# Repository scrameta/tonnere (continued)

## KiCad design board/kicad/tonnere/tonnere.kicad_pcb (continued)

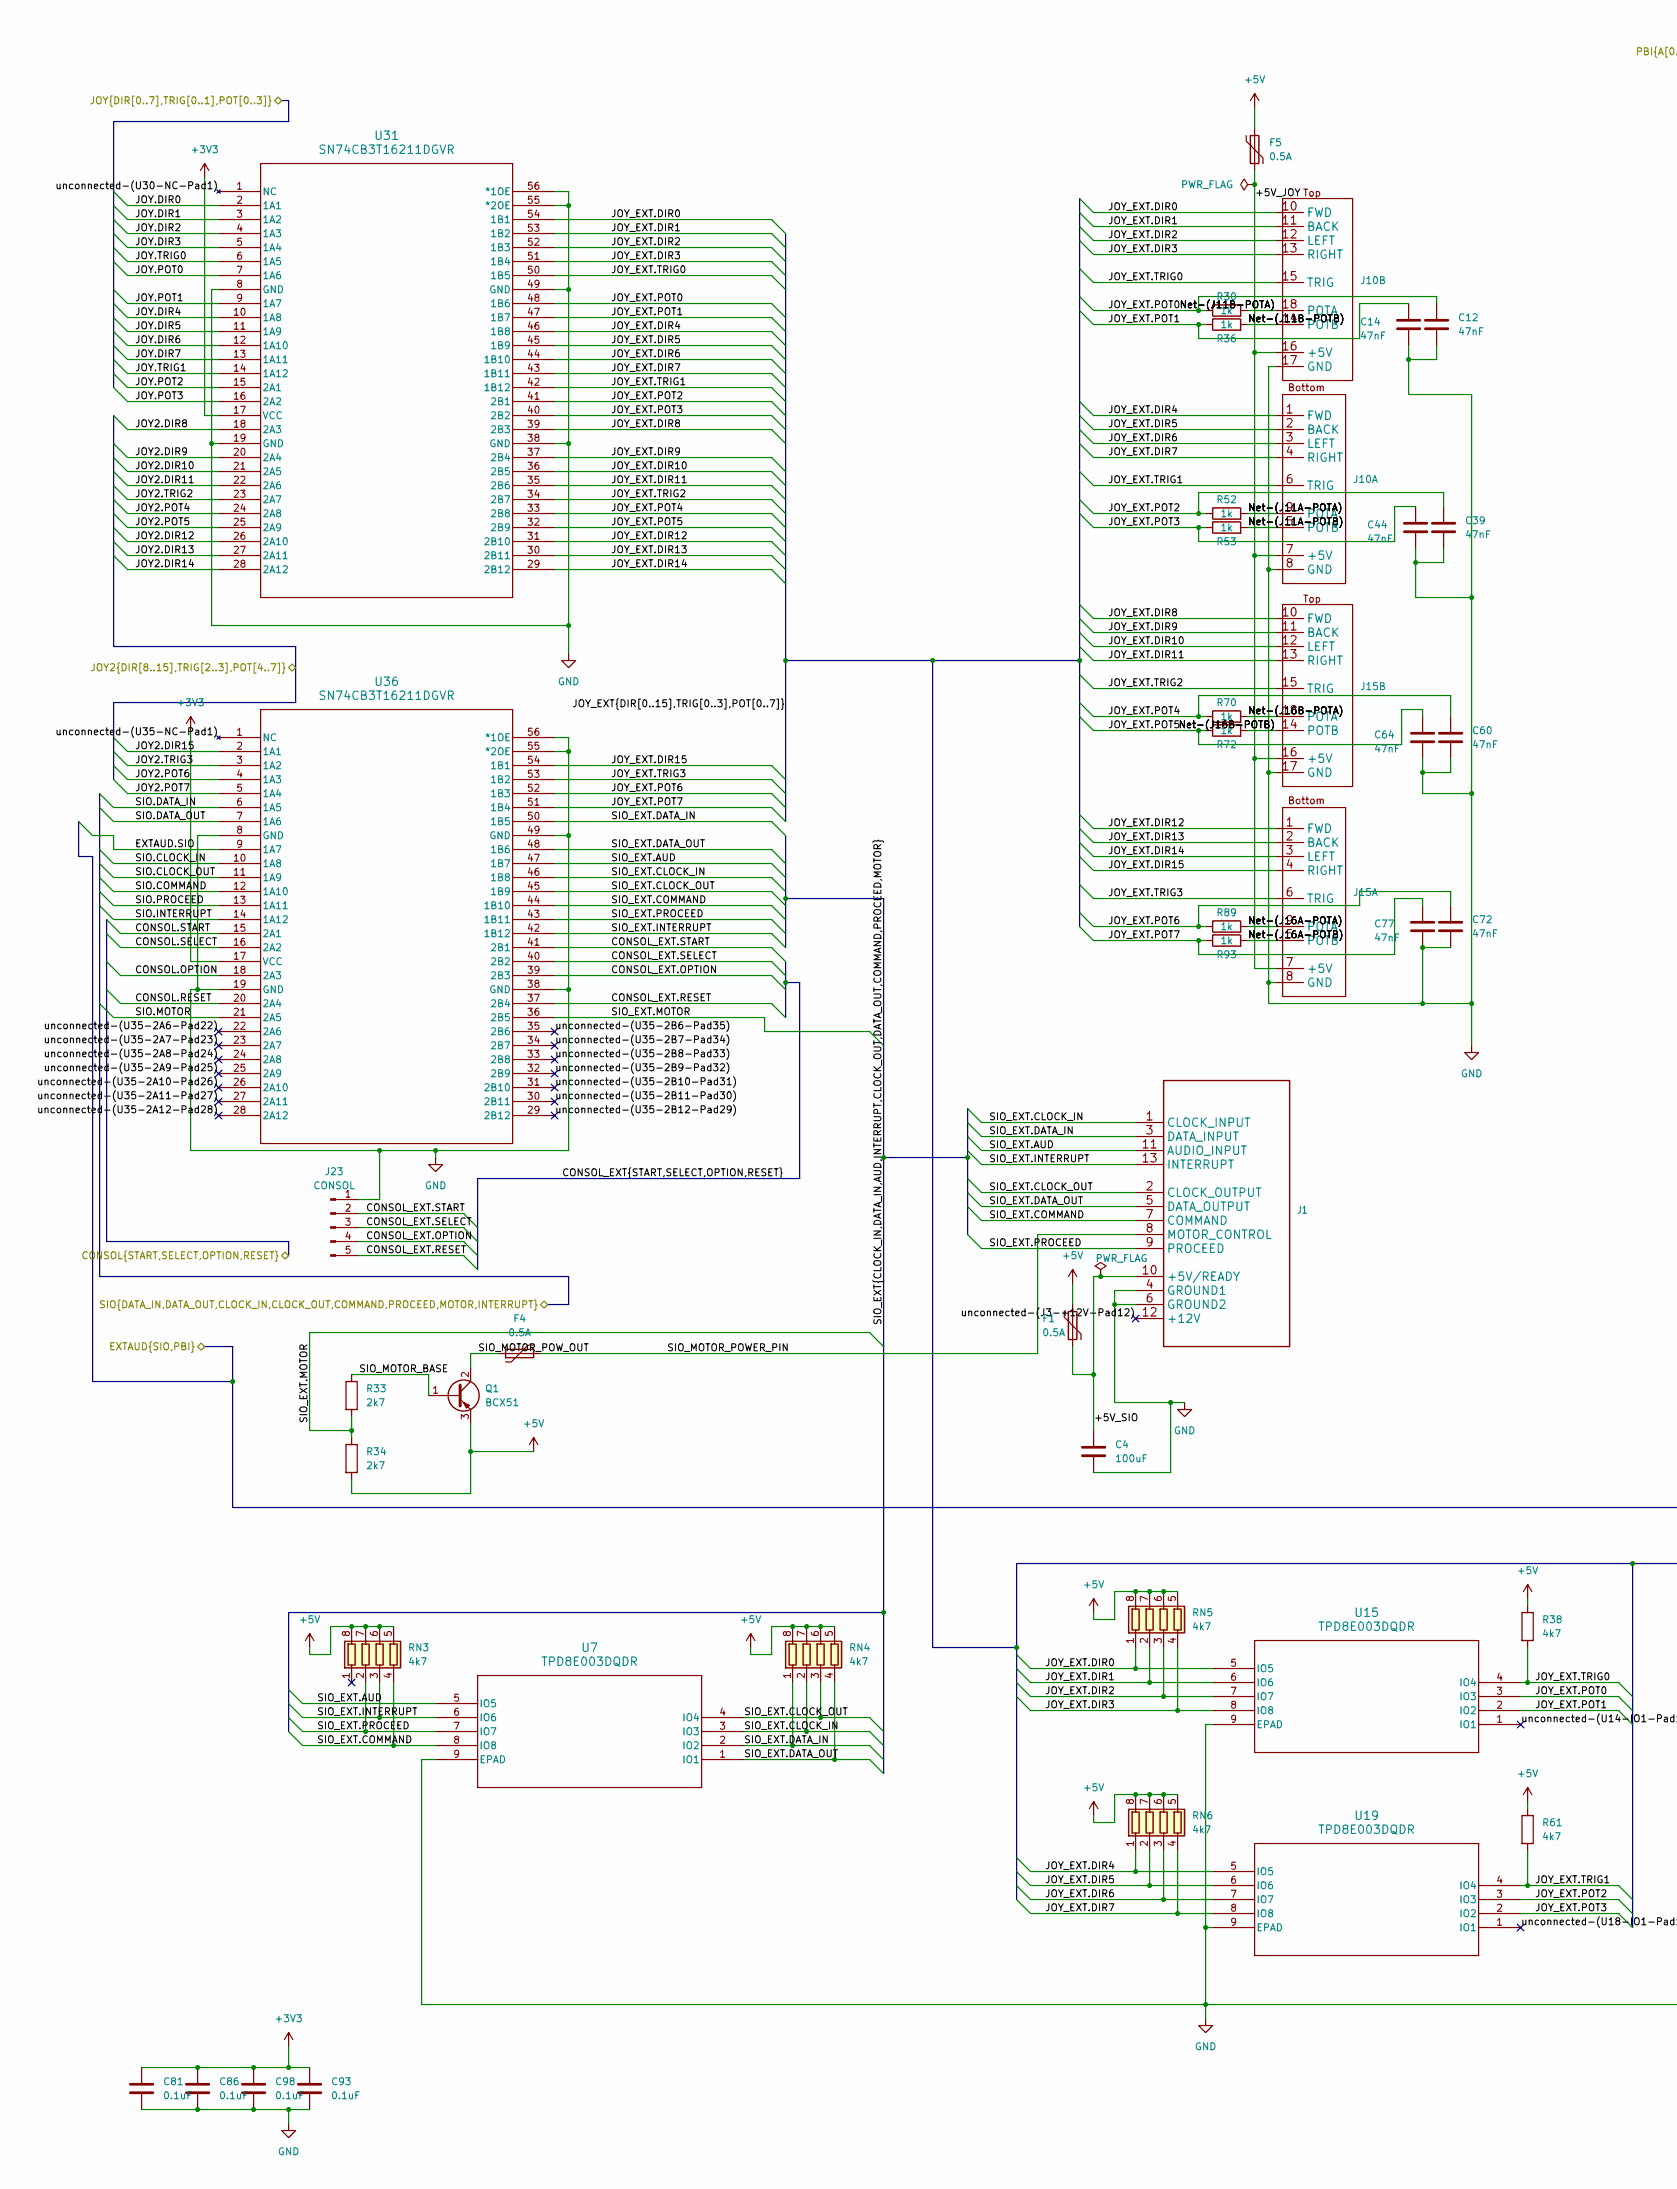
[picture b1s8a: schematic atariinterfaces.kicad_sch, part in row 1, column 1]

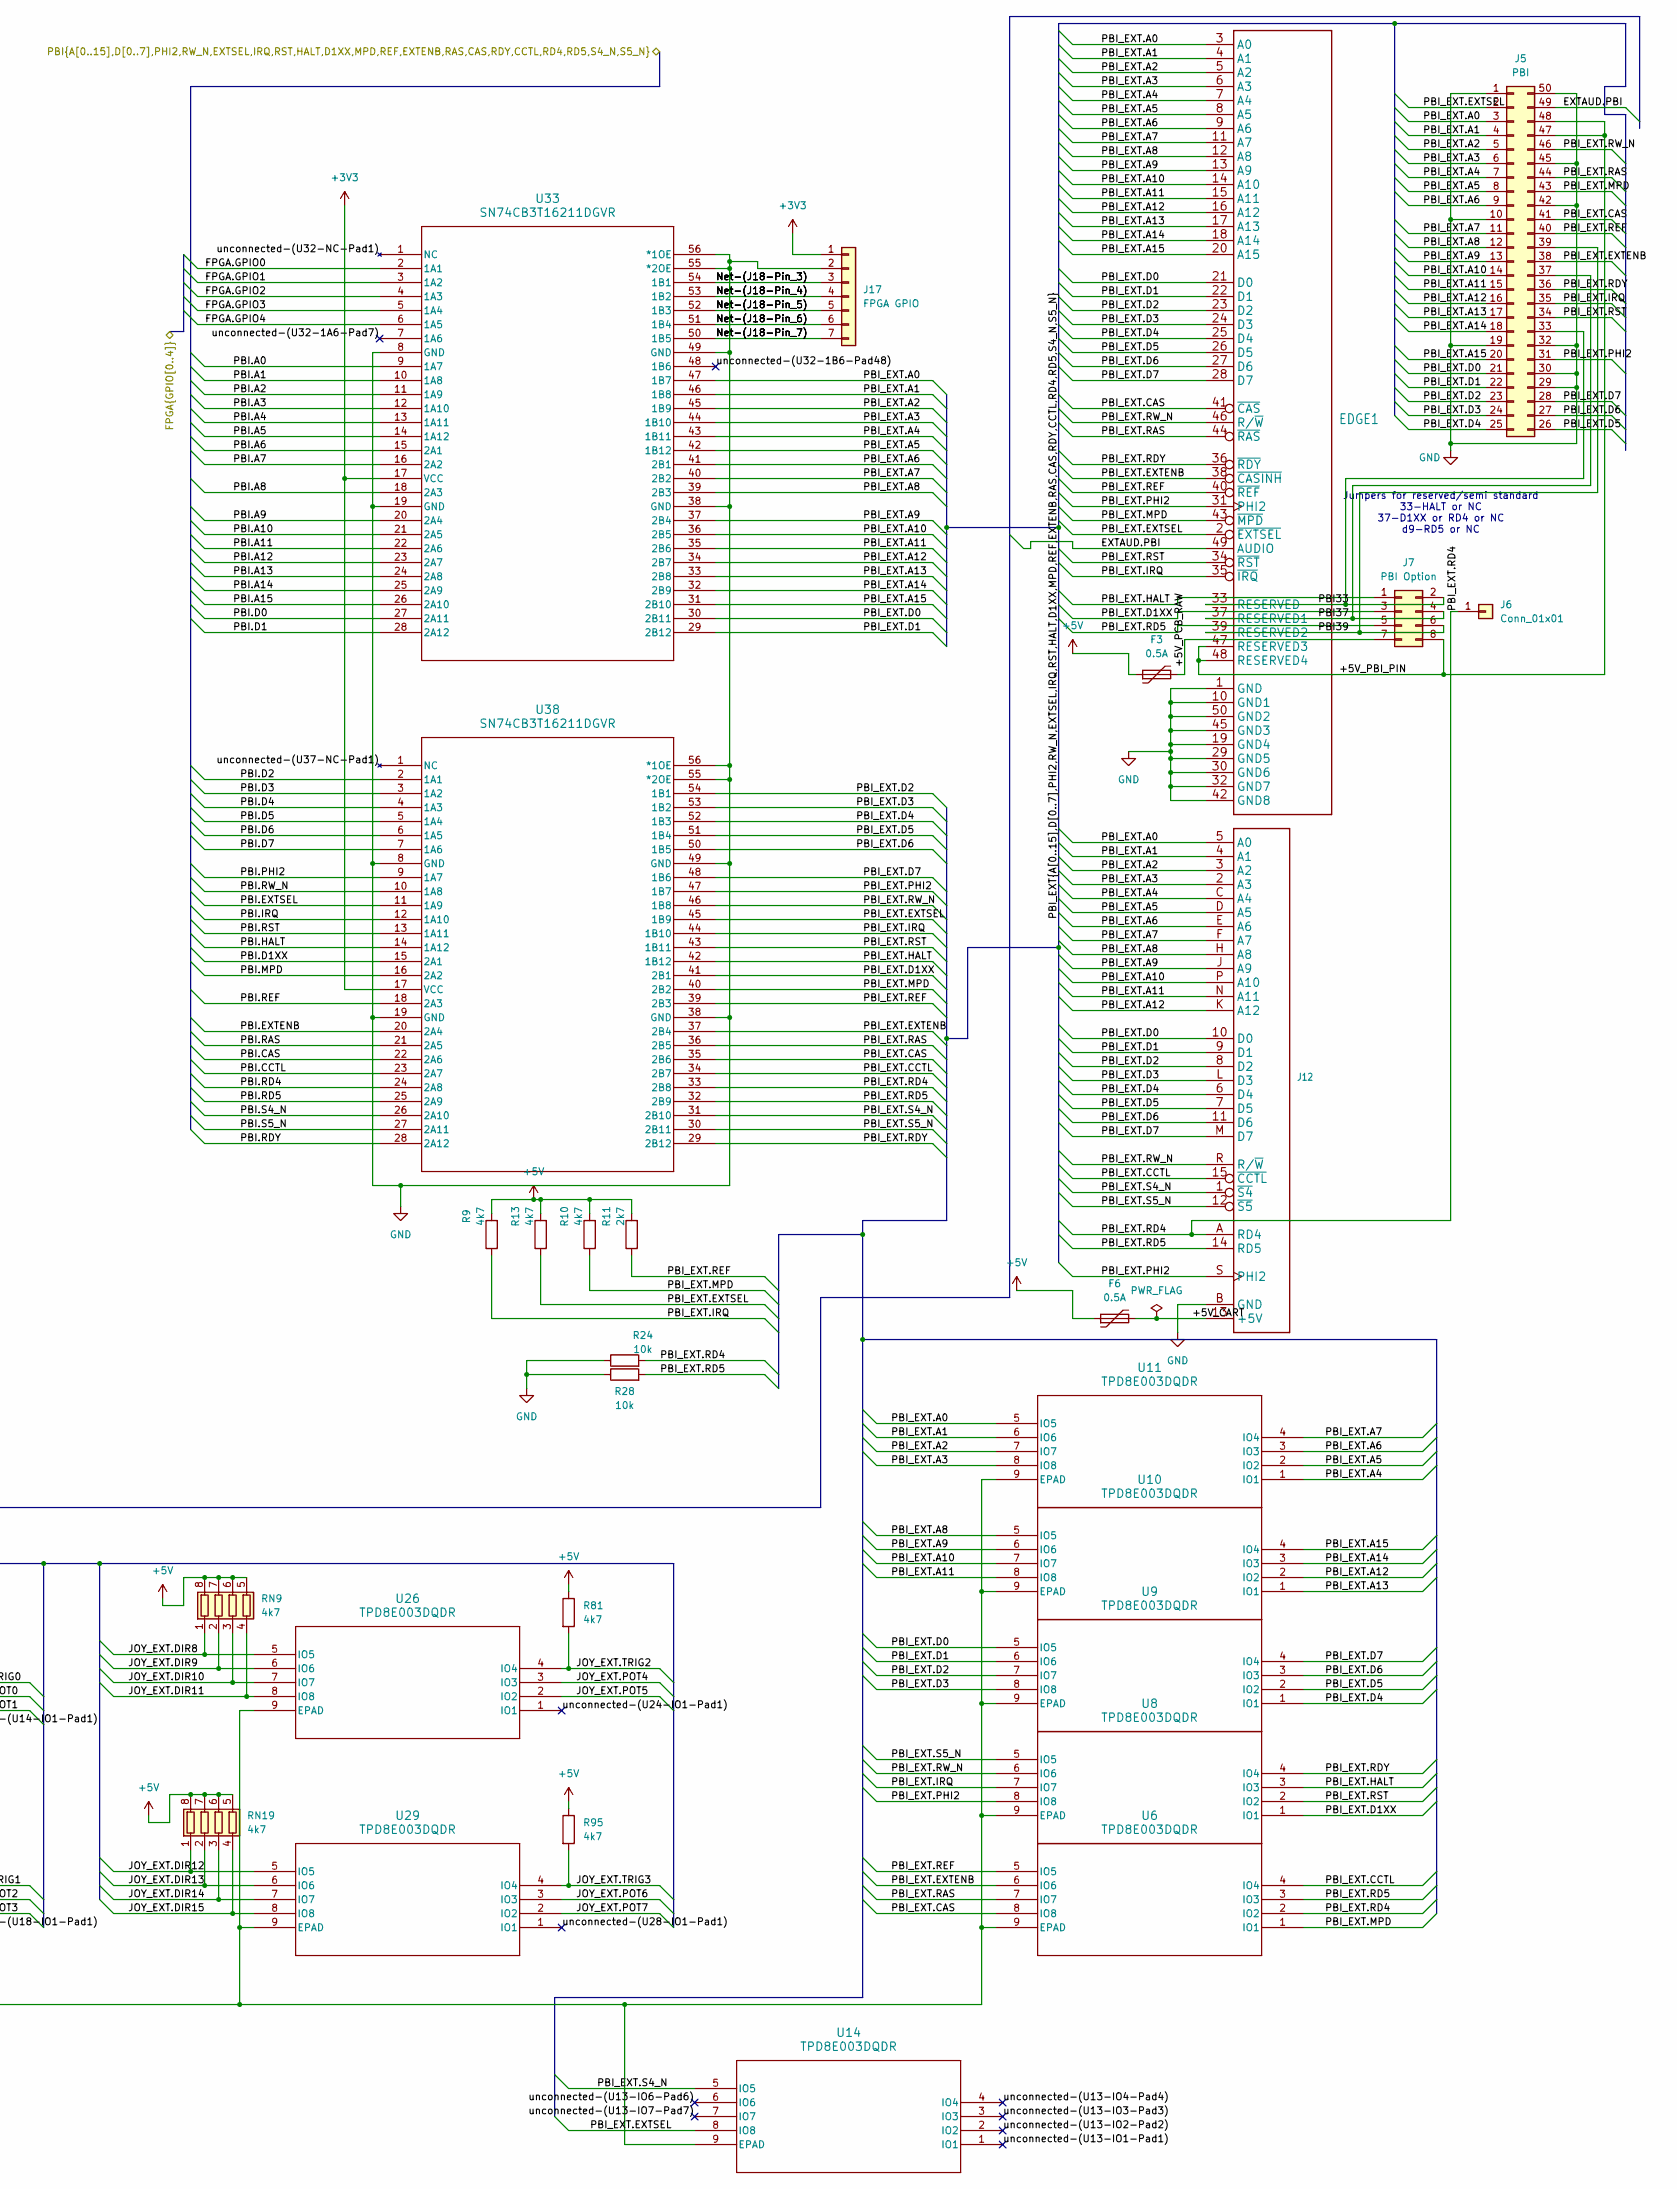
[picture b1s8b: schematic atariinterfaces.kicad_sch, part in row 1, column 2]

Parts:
C4: 100uF; C_1206_3216Metric; LCSC C883598
C12, C14, C39, C44, C60, C64, C72, C77: 47nF; C_0603_1608Metric; LCSC C1622
C81, C86, C93, C98: 0.1uF; C_0603_1608Metric; LCSC C14663
EDGE1: PARALLEL_BUS_INTERFACE
F1, F3, F4, F5, F6: 0.5A; R_0603_1608Metric; LCSC C269152
J1: SIO_JACK
J5: PBI; PinHeader_2x25_P2.54mm_Vertical
J6: Conn_01x01; PinSocket_1x01_P2.54mm_Vertical; LCSC C492400
J7: PBI Option; PinSocket_2x04_P2.54mm_Vertical; LCSC C225519
J10, J15: DualDSub9Male; LCSC C5431655
J12: CARTRIDGE_SOCKET_WITH_PLASTIC
J17: FPGA GPIO; PinSocket_1x07_P2.54mm_Vertical; LCSC C225482
J23: CONSOL; PinHeader_1x05_P2.54mm_Vertical; LCSC C225480
Q1: BCX51; SOT-89-3; LCSC C475643
R9, R10, R13, R38, R61, R81, R95: 4k7; R_0603_1608Metric; LCSC C23162
R11, R33, R34: 2k7; R_0603_1608Metric; LCSC C13167
R24, R28: 10k; R_0603_1608Metric; LCSC C25804
R30, R36, R52, R53, R70, R72, R89, R93: 1k; R_0603_1608Metric; LCSC C21190
RN3, RN4, RN5, RN6, RN9, RN19: 4k7; R_Array_Convex_4x0603; LCSC C1980
U6, U7, U8, U9, U10, U11, U14, U15, U19, U26, U29: TPD8E003DQDR; DQD8_1P2X0P4; LCSC C2867469
U31, U33, U36, U38: SN74CB3T16211DGVR; DGV56; LCSC C2674751

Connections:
+3V3: C81.1, C86.1, C93.1, C98.1, J17.1, U31.17 (VCC), U33.17 (VCC), U36.17 (VCC), U38.17 (VCC); also elsewhere on the board
+5V: F1.1, F3.1, F5.1, F6.1, Q1.3 (E), R9.2, R10.2, R11.2, R13.2, R34.2, R38.1, R61.1, R81.1, R95.1, RN3.5 (R4.2), RN3.6 (R3.2), RN3.7 (R2.2), RN3.8 (R1.2), RN4.5 (R4.2), RN4.6 (R3.2), RN4.7 (R2.2), RN4.8 (R1.2), RN5.5 (R4.2), RN5.6 (R3.2), RN5.7 (R2.2), RN5.8 (R1.2), RN6.5 (R4.2), RN6.6 (R3.2), RN6.7 (R2.2), RN6.8 (R1.2), RN9.5 (R4.2), RN9.6 (R3.2), RN9.7 (R2.2), RN9.8 (R1.2), RN19.5 (R4.2), RN19.6 (R3.2), RN19.7 (R2.2), RN19.8 (R1.2); also elsewhere on the board
/AtariInterfaces/+5V_CART: F6.2, J12.13 (+5V)
/AtariInterfaces/+5V_JOY: F5.2, J10.7 (+5V), J10.16 (+5V), J15.7 (+5V), J15.16 (+5V)
/AtariInterfaces/+5V_PBI_PIN: EDGE1.47 (RESERVED3), EDGE1.48 (RESERVED4), J5.47, J5.48, J7.8
/AtariInterfaces/+5V_PCB_RAW: F3.2, J7.7
/AtariInterfaces/+5V_SIO: C4.1, F1.2, J1.10 (+5V/READY)
/AtariInterfaces/CONSOL.OPTION: U36.18 (2A3); also elsewhere on the board
/AtariInterfaces/CONSOL.RESET: U36.20 (2A4); also elsewhere on the board
/AtariInterfaces/CONSOL.SELECT: U36.16 (2A2); also elsewhere on the board
/AtariInterfaces/CONSOL.START: U36.15 (2A1); also elsewhere on the board
/AtariInterfaces/CONSOL_EXT.OPTION: J23.4, U36.39 (2B3)
/AtariInterfaces/CONSOL_EXT.RESET: J23.5, U36.37 (2B4)
/AtariInterfaces/CONSOL_EXT.SELECT: J23.3, U36.40 (2B2)
/AtariInterfaces/CONSOL_EXT.START: J23.2, U36.41 (2B1)
/AtariInterfaces/EXTAUD.PBI: EDGE1.49 (AUDIO), J5.49; also elsewhere on the board
/AtariInterfaces/EXTAUD.SIO: U36.9 (1A7); also elsewhere on the board
/AtariInterfaces/FPGA.GPIO0: U33.2 (1A1); also elsewhere on the board
/AtariInterfaces/FPGA.GPIO1: U33.3 (1A2); also elsewhere on the board
/AtariInterfaces/FPGA.GPIO2: U33.4 (1A3); also elsewhere on the board
/AtariInterfaces/FPGA.GPIO3: U33.5 (1A4); also elsewhere on the board
/AtariInterfaces/FPGA.GPIO4: U33.6 (1A5); also elsewhere on the board
/AtariInterfaces/JOY2.DIR8: U31.18 (2A3); also elsewhere on the board
/AtariInterfaces/JOY2.DIR9: U31.20 (2A4); also elsewhere on the board
/AtariInterfaces/JOY2.DIR10: U31.21 (2A5); also elsewhere on the board
/AtariInterfaces/JOY2.DIR11: U31.22 (2A6); also elsewhere on the board
/AtariInterfaces/JOY2.DIR12: U31.26 (2A10); also elsewhere on the board
/AtariInterfaces/JOY2.DIR13: U31.27 (2A11); also elsewhere on the board
/AtariInterfaces/JOY2.DIR14: U31.28 (2A12); also elsewhere on the board
/AtariInterfaces/JOY2.DIR15: U36.2 (1A1); also elsewhere on the board
/AtariInterfaces/JOY2.POT4: U31.24 (2A8); also elsewhere on the board
/AtariInterfaces/JOY2.POT5: U31.25 (2A9); also elsewhere on the board
/AtariInterfaces/JOY2.POT6: U36.4 (1A3); also elsewhere on the board
/AtariInterfaces/JOY2.POT7: U36.5 (1A4); also elsewhere on the board
/AtariInterfaces/JOY2.TRIG2: U31.23 (2A7); also elsewhere on the board
/AtariInterfaces/JOY2.TRIG3: U36.3 (1A2); also elsewhere on the board
/AtariInterfaces/JOY.DIR0: U31.2 (1A1); also elsewhere on the board
/AtariInterfaces/JOY.DIR1: U31.3 (1A2); also elsewhere on the board
/AtariInterfaces/JOY.DIR2: U31.4 (1A3); also elsewhere on the board
/AtariInterfaces/JOY.DIR3: U31.5 (1A4); also elsewhere on the board
/AtariInterfaces/JOY.DIR4: U31.10 (1A8); also elsewhere on the board
/AtariInterfaces/JOY.DIR5: U31.11 (1A9); also elsewhere on the board
/AtariInterfaces/JOY.DIR6: U31.12 (1A10); also elsewhere on the board
/AtariInterfaces/JOY.DIR7: U31.13 (1A11); also elsewhere on the board
/AtariInterfaces/JOY.POT0: U31.7 (1A6); also elsewhere on the board
/AtariInterfaces/JOY.POT1: U31.9 (1A7); also elsewhere on the board
/AtariInterfaces/JOY.POT2: U31.15 (2A1); also elsewhere on the board
/AtariInterfaces/JOY.POT3: U31.16 (2A2); also elsewhere on the board
/AtariInterfaces/JOY.TRIG0: U31.6 (1A5); also elsewhere on the board
/AtariInterfaces/JOY.TRIG1: U31.14 (1A12); also elsewhere on the board
/AtariInterfaces/JOY_EXT.DIR0: J10.10 (FWD), RN5.1 (R1.1), U15.5 (IO5), U31.54 (1B1)
/AtariInterfaces/JOY_EXT.DIR1: J10.11 (BACK), RN5.2 (R2.1), U15.6 (IO6), U31.53 (1B2)
/AtariInterfaces/JOY_EXT.DIR2: J10.12 (LEFT), RN5.3 (R3.1), U15.7 (IO7), U31.52 (1B3)
/AtariInterfaces/JOY_EXT.DIR3: J10.13 (RIGHT), RN5.4 (R4.1), U15.8 (IO8), U31.51 (1B4)
/AtariInterfaces/JOY_EXT.DIR4: J10.1 (FWD), RN6.1 (R1.1), U19.5 (IO5), U31.46 (1B8)
/AtariInterfaces/JOY_EXT.DIR5: J10.2 (BACK), RN6.2 (R2.1), U19.6 (IO6), U31.45 (1B9)
/AtariInterfaces/JOY_EXT.DIR6: J10.3 (LEFT), RN6.3 (R3.1), U19.7 (IO7), U31.44 (1B10)
/AtariInterfaces/JOY_EXT.DIR7: J10.4 (RIGHT), RN6.4 (R4.1), U19.8 (IO8), U31.43 (1B11)
/AtariInterfaces/JOY_EXT.DIR8: J15.10 (FWD), RN9.1 (R1.1), U26.5 (IO5), U31.39 (2B3)
/AtariInterfaces/JOY_EXT.DIR9: J15.11 (BACK), RN9.2 (R2.1), U26.6 (IO6), U31.37 (2B4)
/AtariInterfaces/JOY_EXT.DIR10: J15.12 (LEFT), RN9.3 (R3.1), U26.7 (IO7), U31.36 (2B5)
/AtariInterfaces/JOY_EXT.DIR11: J15.13 (RIGHT), RN9.4 (R4.1), U26.8 (IO8), U31.35 (2B6)
/AtariInterfaces/JOY_EXT.DIR12: J15.1 (FWD), RN19.1 (R1.1), U29.5 (IO5), U31.31 (2B10)
/AtariInterfaces/JOY_EXT.DIR13: J15.2 (BACK), RN19.2 (R2.1), U29.6 (IO6), U31.30 (2B11)
/AtariInterfaces/JOY_EXT.DIR14: J15.3 (LEFT), RN19.3 (R3.1), U29.7 (IO7), U31.29 (2B12)
/AtariInterfaces/JOY_EXT.DIR15: J15.4 (RIGHT), RN19.4 (R4.1), U29.8 (IO8), U36.54 (1B1)
/AtariInterfaces/JOY_EXT.POT0: C12.1, R30.1, U15.3 (IO3), U31.48 (1B6)
/AtariInterfaces/JOY_EXT.POT1: C14.1, R36.1, U15.2 (IO2), U31.47 (1B7)
/AtariInterfaces/JOY_EXT.POT2: C39.1, R52.1, U19.3 (IO3), U31.41 (2B1)
/AtariInterfaces/JOY_EXT.POT3: C44.1, R53.1, U19.2 (IO2), U31.40 (2B2)
/AtariInterfaces/JOY_EXT.POT4: C60.1, R70.1, U26.3 (IO3), U31.33 (2B8)
/AtariInterfaces/JOY_EXT.POT5: C64.1, R72.1, U26.2 (IO2), U31.32 (2B9)
/AtariInterfaces/JOY_EXT.POT6: C72.1, R89.1, U29.3 (IO3), U36.52 (1B3)
/AtariInterfaces/JOY_EXT.POT7: C77.1, R93.1, U29.2 (IO2), U36.51 (1B4)
/AtariInterfaces/JOY_EXT.TRIG0: J10.15 (TRIG), R38.2, U15.4 (IO4), U31.50 (1B5)
/AtariInterfaces/JOY_EXT.TRIG1: J10.6 (TRIG), R61.2, U19.4 (IO4), U31.42 (1B12)
/AtariInterfaces/JOY_EXT.TRIG2: J15.15 (TRIG), R81.2, U26.4 (IO4), U31.34 (2B7)
/AtariInterfaces/JOY_EXT.TRIG3: J15.6 (TRIG), R95.2, U29.4 (IO4), U36.53 (1B2)
/AtariInterfaces/Net-(J11A-POTA): J10.9 (POTA), R52.2
/AtariInterfaces/Net-(J11A-POTB): J10.5 (POTB), R53.2
/AtariInterfaces/Net-(J11B-POTA): J10.18 (POTA), R30.2
/AtariInterfaces/Net-(J11B-POTB): J10.14 (POTB), R36.2
/AtariInterfaces/Net-(J16A-POTA): J15.9 (POTA), R89.2
/AtariInterfaces/Net-(J16A-POTB): J15.5 (POTB), R93.2
/AtariInterfaces/Net-(J16B-POTA): J15.18 (POTA), R70.2
/AtariInterfaces/Net-(J16B-POTB): J15.14 (POTB), R72.2
/AtariInterfaces/Net-(J18-Pin_3): J17.3, U33.54 (1B1)
/AtariInterfaces/Net-(J18-Pin_4): J17.4, U33.53 (1B2)
/AtariInterfaces/Net-(J18-Pin_5): J17.5, U33.52 (1B3)
/AtariInterfaces/Net-(J18-Pin_6): J17.6, U33.51 (1B4)
/AtariInterfaces/Net-(J18-Pin_7): J17.7, U33.50 (1B5)
/AtariInterfaces/PBI33: EDGE1.33 (RESERVED), J5.33, J7.2
/AtariInterfaces/PBI37: EDGE1.37 (RESERVED1), J5.37, J7.4
/AtariInterfaces/PBI39: EDGE1.39 (RESERVED2), J5.39, J7.6
/AtariInterfaces/PBI.A0: U33.9 (1A7); also elsewhere on the board
/AtariInterfaces/PBI.A1: U33.10 (1A8); also elsewhere on the board
/AtariInterfaces/PBI.A2: U33.11 (1A9); also elsewhere on the board
/AtariInterfaces/PBI.A3: U33.12 (1A10); also elsewhere on the board
/AtariInterfaces/PBI.A4: U33.13 (1A11); also elsewhere on the board
/AtariInterfaces/PBI.A5: U33.14 (1A12); also elsewhere on the board
/AtariInterfaces/PBI.A6: U33.15 (2A1); also elsewhere on the board
/AtariInterfaces/PBI.A7: U33.16 (2A2); also elsewhere on the board
/AtariInterfaces/PBI.A8: U33.18 (2A3); also elsewhere on the board
/AtariInterfaces/PBI.A9: U33.20 (2A4); also elsewhere on the board
/AtariInterfaces/PBI.A10: U33.21 (2A5); also elsewhere on the board
/AtariInterfaces/PBI.A11: U33.22 (2A6); also elsewhere on the board
/AtariInterfaces/PBI.A12: U33.23 (2A7); also elsewhere on the board
/AtariInterfaces/PBI.A13: U33.24 (2A8); also elsewhere on the board
/AtariInterfaces/PBI.A14: U33.25 (2A9); also elsewhere on the board
/AtariInterfaces/PBI.A15: U33.26 (2A10); also elsewhere on the board
/AtariInterfaces/PBI.CAS: U38.22 (2A6); also elsewhere on the board
/AtariInterfaces/PBI.CCTL: U38.23 (2A7); also elsewhere on the board
/AtariInterfaces/PBI.D0: U33.27 (2A11); also elsewhere on the board
/AtariInterfaces/PBI.D1: U33.28 (2A12); also elsewhere on the board
/AtariInterfaces/PBI.D1XX: U38.15 (2A1); also elsewhere on the board
/AtariInterfaces/PBI.D2: U38.2 (1A1); also elsewhere on the board
/AtariInterfaces/PBI.D3: U38.3 (1A2); also elsewhere on the board
/AtariInterfaces/PBI.D4: U38.4 (1A3); also elsewhere on the board
/AtariInterfaces/PBI.D5: U38.5 (1A4); also elsewhere on the board
/AtariInterfaces/PBI.D6: U38.6 (1A5); also elsewhere on the board
/AtariInterfaces/PBI.D7: U38.7 (1A6); also elsewhere on the board
/AtariInterfaces/PBI.EXTENB: U38.20 (2A4); also elsewhere on the board
/AtariInterfaces/PBI.EXTSEL: U38.11 (1A9); also elsewhere on the board
/AtariInterfaces/PBI.HALT: U38.14 (1A12); also elsewhere on the board
/AtariInterfaces/PBI.IRQ: U38.12 (1A10); also elsewhere on the board
/AtariInterfaces/PBI.MPD: U38.16 (2A2); also elsewhere on the board
/AtariInterfaces/PBI.PHI2: U38.9 (1A7); also elsewhere on the board
/AtariInterfaces/PBI.RAS: U38.21 (2A5); also elsewhere on the board
/AtariInterfaces/PBI.RD4: U38.24 (2A8); also elsewhere on the board
/AtariInterfaces/PBI.RD5: U38.25 (2A9); also elsewhere on the board
/AtariInterfaces/PBI.RDY: U38.28 (2A12); also elsewhere on the board
/AtariInterfaces/PBI.REF: U38.18 (2A3); also elsewhere on the board
/AtariInterfaces/PBI.RST: U38.13 (1A11); also elsewhere on the board
/AtariInterfaces/PBI.RW_N: U38.10 (1A8); also elsewhere on the board
/AtariInterfaces/PBI.S4_N: U38.26 (2A10); also elsewhere on the board
/AtariInterfaces/PBI.S5_N: U38.27 (2A11); also elsewhere on the board
/AtariInterfaces/PBI_EXT.A0: EDGE1.3 (A0), J5.3, J12.5 (A0), U11.5 (IO5), U33.47 (1B7)
/AtariInterfaces/PBI_EXT.A1: EDGE1.4 (A1), J5.4, J12.4 (A1), U11.6 (IO6), U33.46 (1B8)
/AtariInterfaces/PBI_EXT.A2: EDGE1.5 (A2), J5.5, J12.3 (A2), U11.7 (IO7), U33.45 (1B9)
/AtariInterfaces/PBI_EXT.A3: EDGE1.6 (A3), J5.6, J12.2 (A3), U11.8 (IO8), U33.44 (1B10)
/AtariInterfaces/PBI_EXT.A4: EDGE1.7 (A4), J5.7, J12.C (A4), U11.1 (IO1), U33.43 (1B11)
/AtariInterfaces/PBI_EXT.A5: EDGE1.8 (A5), J5.8, J12.D (A5), U11.2 (IO2), U33.42 (1B12)
/AtariInterfaces/PBI_EXT.A6: EDGE1.9 (A6), J5.9, J12.E (A6), U11.3 (IO3), U33.41 (2B1)
/AtariInterfaces/PBI_EXT.A7: EDGE1.11 (A7), J5.11, J12.F (A7), U11.4 (IO4), U33.40 (2B2)
/AtariInterfaces/PBI_EXT.A8: EDGE1.12 (A8), J5.12, J12.H (A8), U10.5 (IO5), U33.39 (2B3)
/AtariInterfaces/PBI_EXT.A9: EDGE1.13 (A9), J5.13, J12.J (A9), U10.6 (IO6), U33.37 (2B4)
/AtariInterfaces/PBI_EXT.A10: EDGE1.14 (A10), J5.14, J12.P (A10), U10.7 (IO7), U33.36 (2B5)
/AtariInterfaces/PBI_EXT.A11: EDGE1.15 (A11), J5.15, J12.N (A11), U10.8 (IO8), U33.35 (2B6)
/AtariInterfaces/PBI_EXT.A12: EDGE1.16 (A12), J5.16, J12.K (A12), U10.2 (IO2), U33.34 (2B7)
/AtariInterfaces/PBI_EXT.A13: EDGE1.17 (A13), J5.17, U10.1 (IO1), U33.33 (2B8)
/AtariInterfaces/PBI_EXT.A14: EDGE1.18 (A14), J5.18, U10.3 (IO3), U33.32 (2B9)
/AtariInterfaces/PBI_EXT.A15: EDGE1.20 (A15), J5.20, U10.4 (IO4), U33.31 (2B10)
/AtariInterfaces/PBI_EXT.CAS: EDGE1.41 (~CAS), J5.41, U6.8 (IO8), U38.35 (2B6)
/AtariInterfaces/PBI_EXT.CCTL: J12.15 (~CCTL), U6.4 (IO4), U38.34 (2B7)
/AtariInterfaces/PBI_EXT.D0: EDGE1.21 (D0), J5.21, J12.10 (D0), U9.5 (IO5), U33.30 (2B11)
/AtariInterfaces/PBI_EXT.D1: EDGE1.22 (D1), J5.22, J12.9 (D1), U9.6 (IO6), U33.29 (2B12)
/AtariInterfaces/PBI_EXT.D1XX: J7.3, U8.1 (IO1), U38.41 (2B1)
/AtariInterfaces/PBI_EXT.D2: EDGE1.23 (D2), J5.23, J12.8 (D2), U9.7 (IO7), U38.54 (1B1)
/AtariInterfaces/PBI_EXT.D3: EDGE1.24 (D3), J5.24, J12.L (D3), U9.8 (IO8), U38.53 (1B2)
/AtariInterfaces/PBI_EXT.D4: EDGE1.25 (D4), J5.25, J12.6 (D4), U9.1 (IO1), U38.52 (1B3)
/AtariInterfaces/PBI_EXT.D5: EDGE1.26 (D5), J5.26, J12.7 (D5), U9.2 (IO2), U38.51 (1B4)
/AtariInterfaces/PBI_EXT.D6: EDGE1.27 (D6), J5.27, J12.11 (D6), U9.3 (IO3), U38.50 (1B5)
/AtariInterfaces/PBI_EXT.D7: EDGE1.28 (D7), J5.28, J12.M (D7), U9.4 (IO4), U38.48 (1B6)
/AtariInterfaces/PBI_EXT.EXTENB: EDGE1.38 (~CASINH), J5.38, U6.6 (IO6), U38.37 (2B4)
/AtariInterfaces/PBI_EXT.EXTSEL: EDGE1.2 (~EXTSEL), J5.2, R13.1, U14.8 (IO8), U38.45 (1B9)
/AtariInterfaces/PBI_EXT.HALT: J7.1, U8.3 (IO3), U38.42 (1B12)
/AtariInterfaces/PBI_EXT.IRQ: EDGE1.35 (~IRQ), J5.35, R9.1, U8.7 (IO7), U38.44 (1B10)
/AtariInterfaces/PBI_EXT.MPD: EDGE1.43 (~MPD), J5.43, R10.1, U6.1 (IO1), U38.40 (2B2)
/AtariInterfaces/PBI_EXT.PHI2: EDGE1.31 (PHI2), J5.31, J12.S (PHI2), U8.8 (IO8), U38.47 (1B7)
/AtariInterfaces/PBI_EXT.RAS: EDGE1.44 (~RAS), J5.44, U6.7 (IO7), U38.36 (2B5)
/AtariInterfaces/PBI_EXT.RD4: J6.1 (Pin_1_1), J12.A (RD4), R24.2, U6.2 (IO2), U38.33 (2B8)
/AtariInterfaces/PBI_EXT.RD5: J7.5, J12.14 (RD5), R28.2, U6.3 (IO3), U38.32 (2B9)
/AtariInterfaces/PBI_EXT.RDY: EDGE1.36 (~RDY), J5.36, U8.4 (IO4), U38.29 (2B12)
/AtariInterfaces/PBI_EXT.REF: EDGE1.40 (~REF), J5.40, R11.1, U6.5 (IO5), U38.39 (2B3)
/AtariInterfaces/PBI_EXT.RST: EDGE1.34 (~RST), J5.34, U8.2 (IO2), U38.43 (1B11)
/AtariInterfaces/PBI_EXT.RW_N: EDGE1.46 (R/~W), J5.46, J12.R (R/~W), U8.6 (IO6), U38.46 (1B8)
/AtariInterfaces/PBI_EXT.S4_N: J12.1 (~S4), U14.5 (IO5), U38.31 (2B10)
/AtariInterfaces/PBI_EXT.S5_N: J12.12 (~S5), U8.5 (IO5), U38.30 (2B11)
/AtariInterfaces/SIO.CLOCK_IN: U36.10 (1A8); also elsewhere on the board
/AtariInterfaces/SIO.CLOCK_OUT: U36.11 (1A9); also elsewhere on the board
/AtariInterfaces/SIO.COMMAND: U36.12 (1A10); also elsewhere on the board
/AtariInterfaces/SIO.DATA_IN: U36.6 (1A5); also elsewhere on the board
/AtariInterfaces/SIO.DATA_OUT: U36.7 (1A6); also elsewhere on the board
/AtariInterfaces/SIO.INTERRUPT: U36.14 (1A12); also elsewhere on the board
/AtariInterfaces/SIO.MOTOR: U36.21 (2A5); also elsewhere on the board
/AtariInterfaces/SIO.PROCEED: U36.13 (1A11); also elsewhere on the board
/AtariInterfaces/SIO_EXT.AUD: J1.11 (AUDIO_INPUT), U7.5 (IO5), U36.47 (1B7)
/AtariInterfaces/SIO_EXT.CLOCK_IN: J1.1 (CLOCK_INPUT), RN4.2 (R2.1), U7.3 (IO3), U36.46 (1B8)
/AtariInterfaces/SIO_EXT.CLOCK_OUT: J1.2 (CLOCK_OUTPUT), RN4.3 (R3.1), U7.4 (IO4), U36.45 (1B9)
/AtariInterfaces/SIO_EXT.COMMAND: J1.7 (COMMAND), RN3.4 (R4.1), U7.8 (IO8), U36.44 (1B10)
/AtariInterfaces/SIO_EXT.DATA_IN: J1.3 (DATA_INPUT), RN4.1 (R1.1), U7.2 (IO2), U36.50 (1B5)
/AtariInterfaces/SIO_EXT.DATA_OUT: J1.5 (DATA_OUTPUT), RN4.4 (R4.1), U7.1 (IO1), U36.48 (1B6)
/AtariInterfaces/SIO_EXT.INTERRUPT: J1.13 (INTERRUPT), RN3.3 (R3.1), U7.6 (IO6), U36.42 (1B12)
/AtariInterfaces/SIO_EXT.MOTOR: R33.2, R34.1, U36.36 (2B5)
/AtariInterfaces/SIO_EXT.PROCEED: J1.9 (PROCEED), RN3.2 (R2.1), U7.7 (IO7), U36.43 (1B11)
/AtariInterfaces/SIO_MOTOR_BASE: Q1.1 (B), R33.1
/AtariInterfaces/SIO_MOTOR_POWER_PIN: F4.2, J1.8 (MOTOR_CONTROL)
/AtariInterfaces/SIO_MOTOR_POW_OUT: F4.1, Q1.2 (C)
/AtariInterfaces/unconnected-(J3-+12V-Pad12): J1.12 (+12V)
/AtariInterfaces/unconnected-(U13-IO1-Pad1): U14.1 (IO1)
/AtariInterfaces/unconnected-(U13-IO2-Pad2): U14.2 (IO2)
/AtariInterfaces/unconnected-(U13-IO3-Pad3): U14.3 (IO3)
/AtariInterfaces/unconnected-(U13-IO4-Pad4): U14.4 (IO4)
/AtariInterfaces/unconnected-(U13-IO6-Pad6): U14.6 (IO6)
/AtariInterfaces/unconnected-(U13-IO7-Pad7): U14.7 (IO7)
/AtariInterfaces/unconnected-(U14-IO1-Pad1): U15.1 (IO1)
/AtariInterfaces/unconnected-(U18-IO1-Pad1): U19.1 (IO1)
/AtariInterfaces/unconnected-(U24-IO1-Pad1): U26.1 (IO1)
/AtariInterfaces/unconnected-(U28-IO1-Pad1): U29.1 (IO1)
/AtariInterfaces/unconnected-(U32-1A6-Pad7): U33.7 (1A6)
/AtariInterfaces/unconnected-(U32-1B6-Pad48): U33.48 (1B6)
/AtariInterfaces/unconnected-(U35-2A6-Pad22): U36.22 (2A6)
/AtariInterfaces/unconnected-(U35-2A7-Pad23): U36.23 (2A7)
/AtariInterfaces/unconnected-(U35-2A8-Pad24): U36.24 (2A8)
/AtariInterfaces/unconnected-(U35-2A9-Pad25): U36.25 (2A9)
/AtariInterfaces/unconnected-(U35-2A10-Pad26): U36.26 (2A10)
/AtariInterfaces/unconnected-(U35-2A11-Pad27): U36.27 (2A11)
/AtariInterfaces/unconnected-(U35-2A12-Pad28): U36.28 (2A12)
/AtariInterfaces/unconnected-(U35-2B6-Pad35): U36.35 (2B6)
/AtariInterfaces/unconnected-(U35-2B7-Pad34): U36.34 (2B7)
/AtariInterfaces/unconnected-(U35-2B8-Pad33): U36.33 (2B8)
/AtariInterfaces/unconnected-(U35-2B9-Pad32): U36.32 (2B9)
/AtariInterfaces/unconnected-(U35-2B10-Pad31): U36.31 (2B10)
/AtariInterfaces/unconnected-(U35-2B11-Pad30): U36.30 (2B11)
/AtariInterfaces/unconnected-(U35-2B12-Pad29): U36.29 (2B12)
GND: C4.2, C12.2, C14.2, C39.2, C44.2, C60.2, C64.2, C72.2, C77.2, C81.2, C86.2, C93.2, C98.2, EDGE1.1 (GND), EDGE1.10 (GND1), EDGE1.19 (GND4), EDGE1.29 (GND5), EDGE1.30 (GND6), EDGE1.32 (GND7), EDGE1.42 (GND8), EDGE1.45 (GND3), EDGE1.50 (GND2), J1.4 (GROUND1), J1.6 (GROUND2), J5.1, J5.10, J5.19, J5.29, J5.30, J5.32, J5.42, J5.45, J5.50, J10.8 (GND), J10.17 (GND), J12.B (GND), J15.8 (GND), J15.17 (GND), J17.2, J23.1, R24.1, R28.1, U6.9 (EPAD), U7.9 (EPAD), U8.9 (EPAD), U9.9 (EPAD), U10.9 (EPAD), U11.9 (EPAD), U14.9 (EPAD), U15.9 (EPAD), U19.9 (EPAD), U26.9 (EPAD), U29.9 (EPAD), U31.8 (GND), U31.19 (GND), U31.38 (GND), U31.49 (GND), U31.55 (*2OE), U31.56 (*1OE), U33.8 (GND), U33.19 (GND), U33.38 (GND), U33.49 (GND), U33.55 (*2OE), U33.56 (*1OE), U36.8 (GND), U36.19 (GND), U36.38 (GND), U36.49 (GND), U36.55 (*2OE), U36.56 (*1OE), U38.8 (GND), U38.19 (GND), U38.38 (GND), U38.49 (GND), U38.55 (*2OE), U38.56 (*1OE); also elsewhere on the board

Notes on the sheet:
Jumpers for reserved/semi standard 33-HALT or NC 37-D1XX or RD4 or NC d9-RD5 or NC

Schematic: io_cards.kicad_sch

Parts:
C56, C124: 0.1uF; C_0603_1608Metric; LCSC C14663
C57, C123: 100uF; C_1206_3216Metric; LCSC C883598
Card1: HDD; TF-SMD_472192001; Manufacturer Part 472192001; JLC_3DModel 317a26d631154cd7bdb03c9d93c02471
Card2: SD-006M; SD-SMD_SD-006M; Manufacturer Part SD-006M; JLC_3DModel 2b9048296755420789f7f276da73fcbc
RN8, RN20, RN21: 47k; R_Array_Convex_4x0603; LCSC C102673
U47, U48: TPD4E02B04DQA; USON-10_2.5x1.0mm_P0.5mm; LCSC C106794

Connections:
+3V3: C56.1, C57.1, C123.1, C124.1, Card1.4 (VDD), Card2.4 (VDD), RN8.1 (R1.1), RN8.2 (R2.1), RN8.4 (R4.1), RN20.1 (R1.1), RN20.2 (R2.1), RN20.3 (R3.1), RN20.4 (R4.1), RN21.1 (R1.1), RN21.2 (R2.1), RN21.3 (R3.1), RN21.4 (R4.1); also elsewhere on the board
/FPGA/SPI.CS1: Card1.2 (CD/DAT3), RN8.8 (R1.2); also elsewhere on the board
/FPGA/SPI.MISO: Card1.7 (DAT0), RN8.5 (R4.2); also elsewhere on the board
/FPGA/SPI.MOSI: Card1.3 (CMD), RN8.7 (R2.2); also elsewhere on the board
/FPGA/SPI.SCK: Card1.5 (CLK), RN8.6 (R3.2); also elsewhere on the board
/IOCards/SD.CK: Card2.5 (CLK), U47.1 (IO1); also elsewhere on the board
/IOCards/SD.CMD: Card2.2 (CMD), RN20.5 (R4.2), U47.2 (IO2); also elsewhere on the board
/IOCards/SD.D0: Card2.7 (DAT0), RN21.8 (R1.2), U48.4 (IO3); also elsewhere on the board
/IOCards/SD.D1: Card2.8 (DAT1), RN21.7 (R2.2), U48.5 (IO4); also elsewhere on the board
/IOCards/SD.D2: Card2.9 (DAT2), RN20.7 (R2.2), U47.5 (IO4); also elsewhere on the board
/IOCards/SD.D3: Card2.1 (CD/DAT3), RN20.6 (R3.2), U47.4 (IO3); also elsewhere on the board
/IOCards/SD.DETECT: Card2.CD, RN21.6 (R3.2), U48.2 (IO2); also elsewhere on the board
/IOCards/SD.WP: Card2.WP, RN21.5 (R4.2), U48.1 (IO1); also elsewhere on the board
/IOCards/unconnected-(RN12-R1.2-Pad8): RN20.8 (R1.2)
/IOCards/unconnected-(U46-NC-Pad6): U47.6 (NC)
/IOCards/unconnected-(U46-NC-Pad7): U47.7 (NC)
/IOCards/unconnected-(U46-NC-Pad9): U47.9 (NC)
/IOCards/unconnected-(U46-NC-Pad10): U47.10 (NC)
/IOCards/unconnected-(U47-NC-Pad6): U48.6 (NC)
/IOCards/unconnected-(U47-NC-Pad7): U48.7 (NC)
/IOCards/unconnected-(U47-NC-Pad9): U48.9 (NC)
/IOCards/unconnected-(U47-NC-Pad10): U48.10 (NC)
GND: C56.2, C57.2, C123.2, C124.2, Card1.6 (VSS), Card1.9, Card1.10, Card1.11, Card1.12, Card2.3 (Vss1), Card2.6 (Vss2), Card2.12, Card2.13, U47.3 (G), U47.8 (G), U48.3 (G), U48.8 (G); also elsewhere on the board

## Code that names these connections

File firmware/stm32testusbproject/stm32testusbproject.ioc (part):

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Mcu.Name=STM32F407Z(E-G)Tx
Mcu.Package=LQFP144
Mcu.UserName=STM32F407ZGTx
PA0-WKUP.Signal=ADCx_IN0
PA1.Signal=ADCx_IN1
PA11.Mode=Host_Only
PA11.Signal=USB_OTG_FS_DM
PA12.Mode=Host_Only
PA12.Signal=USB_OTG_FS_DP
PA13.Mode=Serial_Wire
PA13.Signal=SYS_JTMS-SWDIO
PA14.Mode=Serial_Wire
PA14.Signal=SYS_JTCK-SWCLK
PA2.Signal=ADCx_IN2
PA3.Signal=ADCx_IN3
PA4.Signal=ADCx_IN4
PA5.Signal=ADCx_IN5
PA6.Signal=ADCx_IN6
PA7.Signal=ADCx_IN7
PB10.Mode=Asynchronous
PB10.Signal=USART3_TX
PB11.Mode=Asynchronous
PB11.Signal=USART3_RX
PB12.GPIOParameters=GPIO_Label
PB12.GPIO_Label=USART_CK
PB12.Signal=GPIO_Input
PB13.GPIOParameters=GPIO_Label
PB13.GPIO_Label=USART_CTS
PB13.Signal=GPIO_Input
PB14.GPIOParameters=GPIO_Label
PB14.GPIO_Label=USART_RTS
PB14.Signal=GPIO_Input
PB3.Mode=Full_Duplex_Master
PB3.Signal=SPI3_SCK
PB4.Mode=Full_Duplex_Master
PB4.Signal=SPI3_MISO
PB5.Mode=Full_Duplex_Master
PB5.Signal=SPI3_MOSI
PB6.GPIOParameters=PinState,GPIO_PuPd,GPIO_Label,GPIO_ModeDefaultOutputPP
PB6.GPIO_Label=SPI_CS1
PB6.GPIO_ModeDefaultOutputPP=GPIO_MODE_OUTPUT_OD
PB6.GPIO_PuPd=GPIO_PULLUP
PB6.PinState=GPIO_PIN_SET
PB6.Signal=GPIO_Output
PB7.GPIOParameters=PinState,GPIO_PuPd,GPIO_Label,GPIO_ModeDefaultOutputPP
PB7.GPIO_Label=SPI_CS2
PB7.GPIO_ModeDefaultOutputPP=GPIO_MODE_OUTPUT_OD
PB7.GPIO_PuPd=GPIO_PULLUP
PB7.PinState=GPIO_PIN_SET
PB7.Signal=GPIO_Output
PB8.Mode=I2C
PB8.Signal=I2C1_SCL
PB9.Mode=I2C
PB9.Signal=I2C1_SDA
PC0.Signal=ADCx_IN10
PC1.Signal=ADCx_IN11
PC10.Mode=SD_4_bits_Wide_bus
PC10.Signal=SDIO_D2
PC11.Mode=SD_4_bits_Wide_bus
PC11.Signal=SDIO_D3
PC12.Mode=SD_4_bits_Wide_bus
PC12.Signal=SDIO_CK
PC13-ANTI_TAMP.GPIOParameters=GPIO_Label
PC13-ANTI_TAMP.GPIO_Label=SD_DETECT
PC13-ANTI_TAMP.Signal=GPIO_Input
PC14-OSC32_IN.Mode=LSE-External-Oscillator
PC14-OSC32_IN.Signal=RCC_OSC32_IN
PC15-OSC32_OUT.Mode=LSE-External-Oscillator
PC15-OSC32_OUT.Signal=RCC_OSC32_OUT
PC2.Signal=ADCx_IN12
PC3.Signal=ADCx_IN13
PC5.GPIOParameters=GPIO_Label
PC5.GPIO_Label=STM_I2CRESET
PC5.Signal=GPIO_Output
PC6.Mode=Asynchronous
PC6.Signal=USART6_TX
PC7.Mode=Asynchronous
PC7.Signal=USART6_RX
PC8.Mode=SD_4_bits_Wide_bus
PC8.Signal=SDIO_D0
PC9.Mode=SD_4_bits_Wide_bus
PC9.Signal=SDIO_D1
PD0.Signal=FSMC_D2_DA2
PD1.Signal=FSMC_D3_DA3
PD10.Signal=FSMC_D15_DA15
PD11.Signal=FSMC_A16_CLE
PD12.Signal=FSMC_A17_ALE
PD13.Signal=FSMC_A18
PD14.Signal=FSMC_D0_DA0
PD15.Signal=FSMC_D1_DA1
PD2.Mode=SD_4_bits_Wide_bus
PD2.Signal=SDIO_CMD
PD3.GPIOParameters=GPIO_Label
PD3.GPIO_Label=SD_WP
PD3.Signal=GPIO_Input
PD4.Signal=FSMC_NOE
PD5.Signal=FSMC_NWE
PD6.Signal=FSMC_NWAIT
PD7.Mode=NorPsramChipSelect1_1
PD7.Signal=FSMC_NE1
PD8.Signal=FSMC_D13_DA13
PD9.Signal=FSMC_D14_DA14
PE0.Signal=FSMC_NBL0
PE1.Signal=FSMC_NBL1
PE10.Signal=FSMC_D7_DA7
PE11.Signal=FSMC_D8_DA8
PE12.Signal=FSMC_D9_DA9
PE13.Signal=FSMC_D10_DA10
PE14.Signal=FSMC_D11_DA11
PE15.Signal=FSMC_D12_DA12
PE3.Signal=FSMC_A19
PE4.Signal=FSMC_A20
PE5.Signal=FSMC_A21
PE6.Signal=FSMC_A22
PE7.Signal=FSMC_D4_DA4
PE8.Signal=FSMC_D5_DA5
PE9.Signal=FSMC_D6_DA6
PF0.Signal=FSMC_A0
PF1.Signal=FSMC_A1
PF10.GPIOParameters=GPIO_Label
PF10.GPIO_Label=GPIO5
PF10.Signal=GPIO_Output
PF12.Signal=FSMC_A6
PF13.Signal=FSMC_A7
PF14.Signal=FSMC_A8
PF15.Signal=FSMC_A9
PF2.Signal=FSMC_A2
PF3.Signal=FSMC_A3
PF4.Signal=FSMC_A4
PF5.Signal=FSMC_A5
PF6.GPIOParameters=GPIO_Label
PF6.GPIO_Label=GPIO1
PF6.Signal=GPIO_Output
PF7.GPIOParameters=GPIO_Label
PF7.GPIO_Label=GPIO2
PF7.Signal=GPIO_Output
PF8.GPIOParameters=GPIO_Label
PF8.GPIO_Label=GPIO3
PF8.Signal=GPIO_Output
PF9.GPIOParameters=GPIO_Label
PF9.GPIO_Label=GPIO4
PF9.Signal=GPIO_Output
PG0.Signal=FSMC_A10
PG1.Signal=FSMC_A11
PG11.GPIOParameters=GPIO_Label
PG11.GPIO_Label=FPGA_PS_N
PG11.Signal=GPIO_Input
PG12.GPIOParameters=GPIO_Label
PG12.GPIO_Label=FPGA_IRQ
PG12.Signal=GPIO_Input
PG13.GPIOParameters=GPIO_Label
PG13.GPIO_Label=FPGA_CONFIG_N
PG13.Signal=GPIO_Input
PG14.GPIOParameters=GPIO_Label
PG14.GPIO_Label=FPGA_STATUS_N
PG14.Signal=GPIO_Input
PG15.GPIOParameters=GPIO_Label
PG15.GPIO_Label=FPGA_CONF_DONE
PG15.Signal=GPIO_Input
PG2.Signal=FSMC_A12
PG3.Signal=FSMC_A13
PG4.Signal=FSMC_A14
PG5.Signal=FSMC_A15
PG6.GPIOParameters=GPIO_Label
PG6.GPIO_Label=ESP_BOOT
PG6.Signal=GPIO_Input
PG7.GPIOParameters=GPIO_Label
PG7.GPIO_Label=ESP_EN
PG7.Signal=GPIO_Input
PH0-OSC_IN.Mode=HSE-External-Oscillator
PH0-OSC_IN.Signal=RCC_OSC_IN
PH1-OSC_OUT.Mode=HSE-External-Oscillator
PH1-OSC_OUT.Signal=RCC_OSC_OUT
RCC.HSE_VALUE=8000000
RCC.SYSCLKFreq_VALUE=168000000
RCC.SYSCLKSource=RCC_SYSCLKSOURCE_PLLCLK
board=custom

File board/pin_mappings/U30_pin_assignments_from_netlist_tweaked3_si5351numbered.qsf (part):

set_location_assignment PIN_A3 -to FPGA_IRQ    # /FPGA/FPGA.IRQ
set_location_assignment PIN_A4 -to FPGA_GPIO[4]    # /AtariInterfaces/FPGA.GPIO4
set_location_assignment PIN_A5 -to FSMC_A[8]    # /FPGA/FSMC.A8
set_location_assignment PIN_A6 -to FSMC_A[11]    # /FPGA/FSMC.A11
set_location_assignment PIN_A7 -to FSMC_D[6]    # /FPGA/FSMC.D6
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set_location_assignment PIN_A18 -to PBI_D[0]    # /AtariInterfaces/PBI.D0
set_location_assignment PIN_A19 -to PBI_D[3]    # /AtariInterfaces/PBI.D3
set_location_assignment PIN_A20 -to PBI_D[6]    # /AtariInterfaces/PBI.D6
set_location_assignment PIN_B3 -to FPGA_GPIO[1]    # /AtariInterfaces/FPGA.GPIO1
set_location_assignment PIN_B4 -to FPGA_GPIO[3]    # /AtariInterfaces/FPGA.GPIO3
set_location_assignment PIN_B5 -to FSMC_A[7]    # /FPGA/FSMC.A7
set_location_assignment PIN_B6 -to FSMC_A[10]    # /FPGA/FSMC.A10
set_location_assignment PIN_B7 -to FSMC_D[5]    # /FPGA/FSMC.D5
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set_location_assignment PIN_B20 -to PBI_D[7]    # /AtariInterfaces/PBI.D7
set_location_assignment PIN_B21 -to PBI_PHI[2]    # /AtariInterfaces/PBI.PHI2
set_location_assignment PIN_B22 -to PBI_EXTSEL    # /AtariInterfaces/PBI.EXTSEL
set_location_assignment PIN_C3 -to FPGA_GPIO[0]    # /AtariInterfaces/FPGA.GPIO0
set_location_assignment PIN_C4 -to FPGA_GPIO[2]    # /AtariInterfaces/FPGA.GPIO2
set_location_assignment PIN_C6 -to FSMC_A[9]    # /FPGA/FSMC.A9
set_location_assignment PIN_C7 -to FSMC_D[4]    # /FPGA/FSMC.D4
set_location_assignment PIN_C8 -to FSMC_D[7]    # /FPGA/FSMC.D7
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set_location_assignment PIN_D17 -to PBI_A[12]    # /AtariInterfaces/PBI.A12
set_location_assignment PIN_D19 -to PBI_D[2]    # /AtariInterfaces/PBI.D2
set_location_assignment PIN_D20 -to PBI_CAS    # /AtariInterfaces/PBI.CAS
set_location_assignment PIN_D21 -to PBI_RD[4]    # /AtariInterfaces/PBI.RD4
set_location_assignment PIN_D22 -to PBI_S4_N    # /AtariInterfaces/PBI.S4_N
set_location_assignment PIN_E1 -to VDAC_R    # /FPGA/VDAC.R
set_location_assignment PIN_E2 -to SPI_CS[2]    # /FPGA/SPI.CS2
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set_location_assignment PIN_G22 -to PLL2[1]    # Net-(U30J-CLK5)
set_location_assignment PIN_H11 -to FSMC_NE[1]    # /FPGA/FSMC.NE1
set_location_assignment PIN_H14 -to PBI_A[2]    # /AtariInterfaces/PBI.A2
set_location_assignment PIN_H16 -to PBI_RD[5]    # /AtariInterfaces/PBI.RD5
set_location_assignment PIN_H17 -to PBI_REF    # /AtariInterfaces/PBI.REF
set_location_assignment PIN_H18 -to PBI_RAS    # /AtariInterfaces/PBI.RAS
set_location_assignment PIN_H19 -to PBI_CCTL    # /AtariInterfaces/PBI.CCTL
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set_location_assignment PIN_R1 -to VDAC_VSYNC    # /FPGA/VDAC.VSYNC
set_location_assignment PIN_R2 -to VDAC_HSYNC    # /FPGA/VDAC.HSYNC
set_location_assignment PIN_R5 -to CONSOL_SELECT    # /AtariInterfaces/CONSOL.SELECT
set_location_assignment PIN_R6 -to CONSOL_OPTION    # /AtariInterfaces/CONSOL.OPTION
set_location_assignment PIN_R7 -to CONSOL_RESET    # /AtariInterfaces/CONSOL.RESET
set_location_assignment PIN_R15 -to SRAM2_A[16]    # /FPGA/SRAM2.A16
set_location_assignment PIN_R16 -to SDRAM1_CLK    # /FPGA/SDRAM1.CLK
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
